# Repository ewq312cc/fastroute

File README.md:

# fastroute

**PCB autorouter for KiCad and Specctra DSN** — a Rust port of the
[Freerouting](https://github.com/freerouting/freerouting) PCB autorouter.
(Not related to the FastRoute global router for IC design used in OpenROAD.)

Same algorithms, same input/output (Specctra `.dsn` → `.ses`), same
command line — without Java, several times faster and with a fraction of the memory.

- **Exact mode** (`--parity`) produces SES output byte-identical to Freerouting's
  deterministic mode (source commit `aa909a3`, single-threaded optimizer, count-based
  time limits) on all 20 benchmark boards.
- **Default mode** runs the optimizer in parallel; results are deterministic for any
  thread count.
- **Live view** (`--live`): watch the board being routed in your browser.
- **KiCad plugin** in [`integrations/kicad`](integrations/kicad/README.md).

## What is different from Freerouting

The bug fixes and routing improvements are on by default; `--no-enhancements` switches them
off (the DSN parser fixes stay), `--parity` gives byte-identical Freerouting results. The new
features are used when asked for (an option, or a rule in the KiCad board). Details,
measurements and the reasoning for each change: [docs/IMPROVEMENTS.md](docs/IMPROVEMENTS.md).

### Bugs fixed

| Freerouting behaviour | fastroute |
|---|---|
| The optimizer never runs after the autorouter stopped itself: the stop request stays set, so every optimizer candidate fails to route | The router's own stop is withdrawn before the optimizer |
| When the stagnation rule stops the autorouter, the final tail removal is skipped and unused fanout escapes (via + stub) stay on the board | Tails are removed in every case |
| The optimizer's score is clamped at 0; on boards whose score is below 0 (e.g. DAC2020_bm01) no candidate can ever be accepted | Unclamped scores are compared (bm01: −182 → 107) |
| A connection that ends in a via into its net's plane layer is rejected ("layers disabled"), so plane nets only reach the plane through fanout | Such connections are accepted |
| `ignore_net_classes` is honoured by the autorouter but not by the fanout, which still adds stubs to the ignored nets | No fanout on ignored classes |
| A failing connection rips its whole net on every failure from the second on; unroutable connections make large nets (GND, 3V3) oscillate | Only once per net |
| Class-pair clearances from the DSN only reach the clearance classes named after the net classes, not the pin/SMD classes of the same nets | Applied to all item classes of both net classes |
| Nets with a pad on or outside the board edge (edge connectors, castellated pads, headers across Edge.Cuts) ignore the outline completely, so their traces can run outside the board anywhere | The area outside the outline is a keepout except right around those pads |
| DSN lexer: non-ASCII letters dropped from names, desynchronisation on some quoted strings, a pin token swallowing a character of the next pin | Parsed correctly |

### Routing and optimizer improvements

- **Optimizer on partly routed boards** (Freerouting skips it as soon as one connection is
  unrouted); **greedy passes** that apply every improving candidate instead of one per pass;
  re-routing only the ripped item's nets; skipping connections that were unrouted from the
  start; a time budget equal to the routing time.
- **Parallel autorouting passes** (`router.autorouter.max_threads`) and a **parallel
  optimizer**, deterministic for a given thread count.
- **Multi-start routing** (`--multi-start`): if connections stay unrouted, the autorouter is
  rerun with shuffled orders in parallel and the best result is kept.
- **Undo of bad passes**, stagnation stop for slow passes, fanout that stops when it only
  re-fans, minimum track width for neck-down (`router.min_trace_width_um`).
- **Checkpoints and time limits**: the session file always holds the best board so far;
  `--max-time`, Ctrl+C / SIGTERM stop the run and keep the result.

### New features

- **Live routing view** (`--live[=PORT]`, a checkbox in the KiCad plugin): a local page at
  `http://127.0.0.1:7878` shows the board as it is routed — traces appearing and being ripped
  up, the remaining airlines, progress of each pass, unrouted connections per pass, clearance
  violations, score and the log — with zoom, layer toggles, net highlighting and a Stop
  button that keeps the best result. Served by fastroute itself (no internet needed);
  results are the same with or without it.

- **Length matching** (`--tune`): groups of nets (buses, pair skew) are matched with
  meanders after routing; every meander is clearance-checked, via heights count as in KiCad.
- **Controlled impedance**: trace widths per layer from the board stackup (microstrip,
  stripline, differential), no neck-down for those classes (`--no-neckdown-classes`).
- **Differential pairs** (`--pairs`): pairs are routed first with the second net following
  the first at the pair gap, held while the rest of the board is routed; afterwards the
  shorter net gets meanders until the two lengths match (`--pair-skew`, default 0.1 mm).

### KiCad plugin

The plugin ([`integrations/kicad`](integrations/kicad/README.md)) exports the board, fills
the gaps of KiCad's Specctra export and imports the result:
- `.kicad_dru` rules are carried over: class clearances, per-layer track widths, length and
  skew rules, differential pair gaps; minimum track width and copper-to-edge clearance too.
- Zones, copper texts and rule areas are exported correctly (KiCad exports every zone as a
  plane and every rule area as a keepout); zones are refilled after routing.
- An option shows the routing live in the web browser (see *Live routing view* above).
- `impedance_cli.py` computes controlled-impedance widths and writes the DRC rules.
- Checked with KiCad's own DRC on the KiCad demo boards (see the results table in
  [docs/IMPROVEMENTS.md](docs/IMPROVEMENTS.md)).

## Build and run

```sh
cargo build --release -p fastroute          # or scripts/build-pgo.sh (~15 % faster)
target/release/fastroute -de board.dsn -do board.ses
```

The session file (`-do`) is rewritten with the best board so far whenever routing or
optimizing improves, so a run that is stopped or killed still leaves its best result.
Ctrl+C, SIGTERM and Ctrl+Break stop the run and write the best result (a second signal exits
at once). `fastroute --help` lists the options and the common `--router.*` settings.

Windows x64 build (cross-compiled with MinGW-w64): `scripts/build-windows.sh` →
`dist/windows/fastroute.exe`. Windows ARM64 build (clang-cl + lld-link with the MSVC SDK
from xwin): `scripts/build-windows-arm64.sh` → `dist/windows-arm64/fastroute.exe`. Linux
x64 and arm64 builds (cargo-zigbuild, glibc 2.17): `scripts/build-linux.sh` →
`dist/linux-*/fastroute`. The KiCad package can bundle several platforms:
`integrations/kicad/package.sh --bin <macos binary> macos-arm64 --bin
dist/windows/fastroute.exe windows-x64 --bin dist/windows-arm64/fastroute.exe windows-arm64
--bin dist/linux-x64/fastroute linux-x64 ...`.

### Commands

`fastroute` has six commands next to the original flags above (which keep working unchanged);
all have `--help`, clear errors, exit codes and never overwrite an existing file without `--force`.
Details: [docs/CLI.md](docs/CLI.md).

| Command | |
|---|---|
| `fastroute route board.dsn` | autoroute; writes `board.routed.ses`, exit code 5 if connections remain (`--allow-partial`), `--json` summary; also takes a `.kicad_pcb` through the KiCad adapter |
| `fastroute render -i board.dsn -s routed.ses -o board.png` | the whole board or a region (`--around U1`, `--net NAME`, `--region-mm`, …) as a PNG, offline, with grid, labels and a manifest ([docs/RENDERING.md](docs/RENDERING.md)) |
| `fastroute inspect -i board.dsn -s routed.ses -o inspect.json` | the board as structured data: nets, pads, unrouted connections and violations with coordinates, rules, check statuses ([docs/AI_DATA_FORMAT.md](docs/AI_DATA_FORMAT.md)) |
| `fastroute rules check draft.json --ai-pack pack/` | rule drafts from people, scripts or AI models: a deterministic offline checker (evidence, values that cannot be guessed, no silent loosening of the design, no geometry), a named person's confirmation, and `apply` to pairs / tune / `.kicad_dru` inputs — acceptance stays with the real DRC ([docs/AI_RULES.md](docs/AI_RULES.md)) |
| `fastroute ai-pack -i board.dsn -s routed.ses -o pack/` | pictures + data + rules + KiCad's DRC (if `kicad-cli` is there; otherwise an explicit status, never "passed") in one local directory ([docs/AI_PACK.md](docs/AI_PACK.md)) |
| `fastroute constraints check\|compile\|validate\|report\|export-fastroute\|check-edit ...` | hardware constraint packs (HCP): what a part requires, with page-level evidence, compiled to a deterministic IR that an offline validator and the router both use; a KiCad board is read-only; an AI may edit only a whitelisted area of a fixed base board ([docs/HCP.md](docs/HCP.md), [docs/CLI.md](docs/CLI.md)). `hcp-manager` (`apps/hcp-manager`) manages the documents; the Skill is in `skills/hardware-constraint-design/`; an example pack for the ESP32-S3-WROOM-1-N8R8 is in `hardware-packs/` |

Freerouting's options are accepted: `-mp <passes>`, `--router.<path>=<value>` (e.g.
`--router.optimizer.enabled=false`, `--router.scoring.via_costs=80`); GUI/API options such
as `--gui.enabled` are ignored. fastroute adds:

| Option | Meaning |
|---|---|
| `--parity` | Exact Freerouting results: java-compatible optimizer, count-based time limits |
| `--optimizer-mode=java-compat\|parallel` | Optimizer strategy (default: parallel if more than one thread) |
| `--time-limit-mode=wall\|count\|disabled`, `--time-limit-factor=N` | How Freerouting's internal time limits are evaluated |
| `--router.min_trace_width_um=<w>` | Never neck traces down below this width |
| `--multi-start=N` | Rerun the autorouter with N−1 shuffled orders in parallel if connections remain unrouted (default 4) |
| `--no-enhancements` | Freerouting's behaviour without fastroute's routing/optimizer improvements (see [docs/IMPROVEMENTS.md](docs/IMPROVEMENTS.md)) |
| `--router.autorouter.max_threads=N` | Threads of the parallel autorouting pass (default: all cores; 1 = sequential pass) |
| `--tune=FILE` | Length matching after routing: groups of nets matched with meanders (see `fastroute --help`) |
| `--layer-heights=MM,..` | Height of each copper layer (stackup), so that vias count in length matching |
| `--pairs=FILE` | Differential pairs: routed first, the second net following the first at the pair gap |
| `--no-neckdown-classes=A,B` | Keep the full trace width of these classes at pins (controlled impedance) |
| `--max-time=SECONDS` | Stop after this time and write the best result so far |
| `--router.autorouter.min_passes=N` | The stagnation rules do not stop the autorouter before N passes (for long runs bounded by `--max-time`) |
| `--initial-session=FILE` | Start from the wiring of a session file (e.g. a checkpoint of an earlier run) and continue routing and optimizing it |
| `--live[=PORT]` | Watch the routing live in the web browser (`http://127.0.0.1:7878` by default, opened automatically): traces and airlines as they change, pass progress, unrouted connections per pass, log, and a Stop button. Results are unaffected |
| `--report=FILE` | Write a JSON summary: statistics, timings, every unrouted connection and clearance violation |
| `--diagnose` | With `--report`: route each unrouted connection alone on the loaded board, classifying it as congestion (other traces in the way) or blocked (geometry or rules) |
| `-V`, `--version` | Print the version |
| `-v` | Verbose progress |

## Performance

Full pipeline (autorouter + optimizer), exact mode, 20 benchmark boards
([docs/PERFORMANCE.md](docs/PERFORMANCE.md)):

| | Freerouting (Java) | fastroute | fastroute + PGO |
|---|---|---|---|
| Sum of 20 boards | 2102 s | 510 s | 420 s |
| DAC2020_bm01 | 960 s | 380 s | 310 s |
| CM5_MINIMA_3 | 410 s | 23 s | 20 s |
| Peak memory (typical) | 1–2 GB | 20–300 MB | |

The parallel optimizer mode is another 1.5–3× faster on most boards.

## Layout

| Crate | Contents |
|---|---|
| `fr-dsn` | Specctra S-expression reader and typed DSN model |
| `fr-geom` | Planar geometry (port of `geometry.planar`) |
| `fr-jcompat` | Bit-exact emulation of the Java library behaviour the router depends on |
| `fr-settings` | Router settings, defaults, CLI/DSN settings sources |
| `fr-engine` | Board model, search trees, autorouter, pull-tight/shove/optimizer, DRC, scoring, pipeline |
| `fr-io` | DSN → board loader, post-load processing, SES writer/reader |
| `fastroute` | Command-line tool |

How the port was done and how parity is tested: [docs/PORTING.md](docs/PORTING.md).
The Java reference build and scripts: `scripts/java-parity.sh`, `scripts/parity-route.sh`.

## Support

fastroute is developed in spare time. If it saves you routing hours or a Java setup, you can
support its development through [GitHub Sponsors](https://github.com/sponsors/parisxmas) or
[Open Collective](https://opencollective.com/parismxas). Bug reports with a board that shows
the problem (a `.dsn` file is enough) are just as welcome.

## License

GPL-3.0-or-later ([LICENSE](LICENSE)). fastroute is a derivative work of Freerouting
(GPL-3.0); all credit for the routing algorithms goes to the Freerouting authors. See
[NOTICE](NOTICE) for the attribution, the Freerouting version it is based on, and the
third-party crates.

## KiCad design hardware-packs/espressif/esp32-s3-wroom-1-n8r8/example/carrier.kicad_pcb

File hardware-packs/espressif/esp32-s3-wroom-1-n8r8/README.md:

# ESP32-S3-WROOM-1-N8R8: example hardware constraint pack

A Hardware Constraint Pack for one module, written from the official Espressif documents that were locked on 2026-11-16, with the
checks, reports and tests that go with it. Read `acceptance.md` for what works, what does not and what a person still has to confirm.

**Locked device**: ESP32-S3-WROOM-1-N8R8 (8 MB quad flash, 8 MB octal PSRAM). The variant matters: IO35, IO36 and IO37 are reserved
because of the octal PSRAM, and the other variants of the same datasheet differ.

| File | What it is |
|---|---|
| `workspace/sources.yaml` | the inventory of documents, managed by `hcp-manager`: URL, level, version, SHA-256 of what was read |
| `overlay.template.yaml` → `pack.yaml` | the example's own part (the carrier: outline, mounting holes, the free area, the LED block, the fixed base design). `pack.yaml` is **generated**: this overlay merged with the module pack `espressif/esp32-s3/esp32-s3-wroom-1/n8r8` (its facts: 19 rules, 41 pins, 4 blocks, the antenna keep-out), which itself inherits from the chip pack `espressif/esp32-s3/esp32-s3/qfn56` (`hardware-packs/`). There is one copy of the module's facts, not two; the merged pack has the same 23 rules, 41 pins, 5 blocks and 6 regions as before (compared object by object when this was done) |
| `ir.json` | the compiled Constraint IR |
| `reports/pack-report.zh.md` | the Chinese report: fixed / required / configurable / unknown, with the quoted evidence |
| `reports/validation-legal.{json,zh.md}` | the validation of the legal carrier board |
| `example/` | the made-up carrier board (`carrier.kicad_pcb`, KiCad 8) and its notes, the `open_board` source |
| `eval/retrieval-eval.yaml` | what a search must find, and what it must never return |
| `tools/` | `extract_pin_table.py` (pin table from the datasheet; `--check pack.yaml`), `build_pack.py` (calls `hardware-packs/tools/build_espressif.py`), `regenerate.sh` |

The documents are not in the repository (they are Espressif's). The inventory pins their digests; `hcp-manager` downloads them and
refuses a file that does not match.

## Reproduce

```bash
cargo build --release -p fastroute -p hcp-manager
export PATH="$PWD/target/release:$PATH"
cd hardware-packs/espressif/esp32-s3-wroom-1-n8r8

hcp-manager --workspace workspace sources sync          # download, check the pinned digests
hcp-manager --workspace workspace index build           # derived text blocks (rebuildable)
hcp-manager --workspace workspace search --device ESP32-S3-WROOM-1-N8R8 "Do not leave the EN pin floating"
hcp-manager --workspace workspace evidence verify pack.yaml    # every quotation is on the cited page

fastroute constraints check pack.yaml
fastroute constraints validate --pack pack.yaml --kicad-pcb example/carrier.kicad_pcb --report validation.md   # exit 5: gaps are named
fastroute constraints edit-request --pack pack.yaml --requirement "add a status LED" -o request.json
tools/regenerate.sh                                     # rebuild pack.yaml, ir.json and the reports
```

The whole flow in one run, through the Skill's script:

```bash
python3 ../../../skills/hardware-constraint-design/scripts/hcp_cli.py --workspace workspace \
    pipeline pack.yaml --out /tmp/esp-out --kicad-pcb example/carrier.kicad_pcb
```

Tests: `cargo test -p fastroute --test esp32s3_pack --test esp32s3_documents` (the second one needs `hcp-manager` built and either the
cache or a network; it says so and passes otherwise).

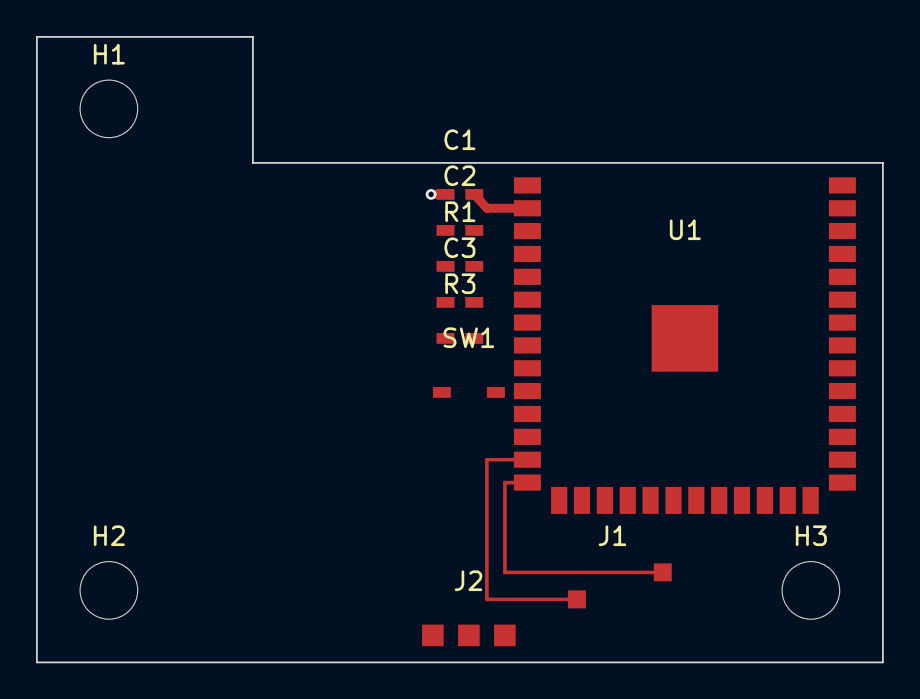
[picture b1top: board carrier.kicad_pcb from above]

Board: 2 copper layers, 47.0 x 34.8 mm, 12 parts (0 on the bottom side), 8 nets.

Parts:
C1: 22uF; C_0805
C2: 100nF; C_0603
C3: 1uF; C_0603
H1, H2, H3: MountingHole; MountingHole_3.2mm
J1: USB; USB_simplified
J2: UART; PinHeader_1x03
R1, R3: 10k; R_0603
SW1: BOOT; SW_SPST
U1: ESP32-S3-WROOM-1-N8R8; ESP32-S3-WROOM-1 (simplified)

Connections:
3V3: C1.1, C2.1, R1.1, R3.1, U1.2
BOOT: R3.2, SW1.1, U1.27
EN: C3.1, R1.2, U1.3
GND: C1.2, C2.2, C3.2, J2.3, SW1.2, U1.1, U1.40, U1.41
UART_RX: J2.2, U1.36
UART_TX: J2.1, U1.37
USB_DM: J1.1, U1.13
USB_DP: J1.2, U1.14

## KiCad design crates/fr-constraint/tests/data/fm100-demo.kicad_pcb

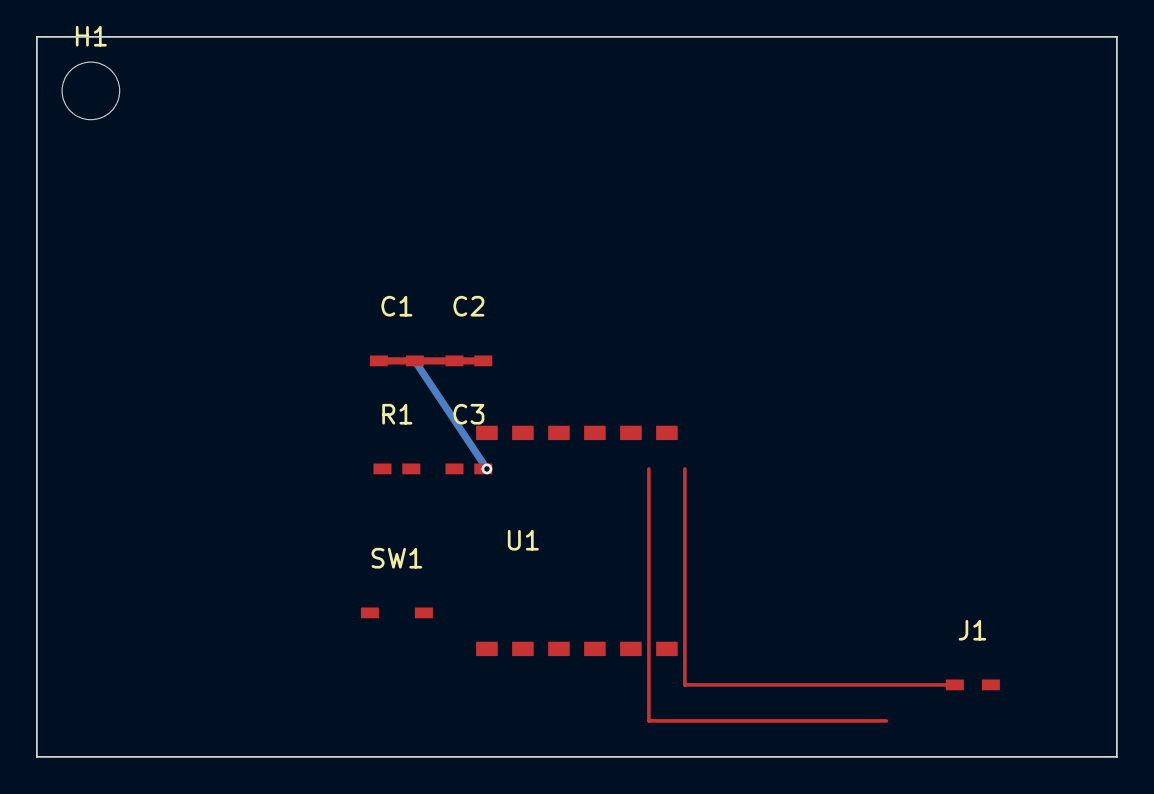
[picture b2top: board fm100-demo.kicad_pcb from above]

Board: 2 copper layers, 60.0 x 40.0 mm, 8 parts (0 on the bottom side), 6 nets.

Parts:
C1: 10uF; C_0805
C2: 100nF; C_0603
C3: 1nF; C_0603
H1: MountingHole; MountingHole_3.2mm
J1: USB; USB_Micro
R1: 10k; R_0603
SW1: BOOT; SW_SPST
U1: FM-100

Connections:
3V3: C1.1, C2.1, R1.1, U1.2
BOOT: SW1.1, U1.4
EN: C3.1, R1.2, U1.3
GND: C1.2, C2.2, C3.2, SW1.2, U1.1, U1.12
USB_DM: J1.2, U1.9
USB_DP: J1.1, U1.8

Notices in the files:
README.md:
License: GPL v3
